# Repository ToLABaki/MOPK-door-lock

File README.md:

# MOPK-door-lock
The door locking mechanism for the MOPK team

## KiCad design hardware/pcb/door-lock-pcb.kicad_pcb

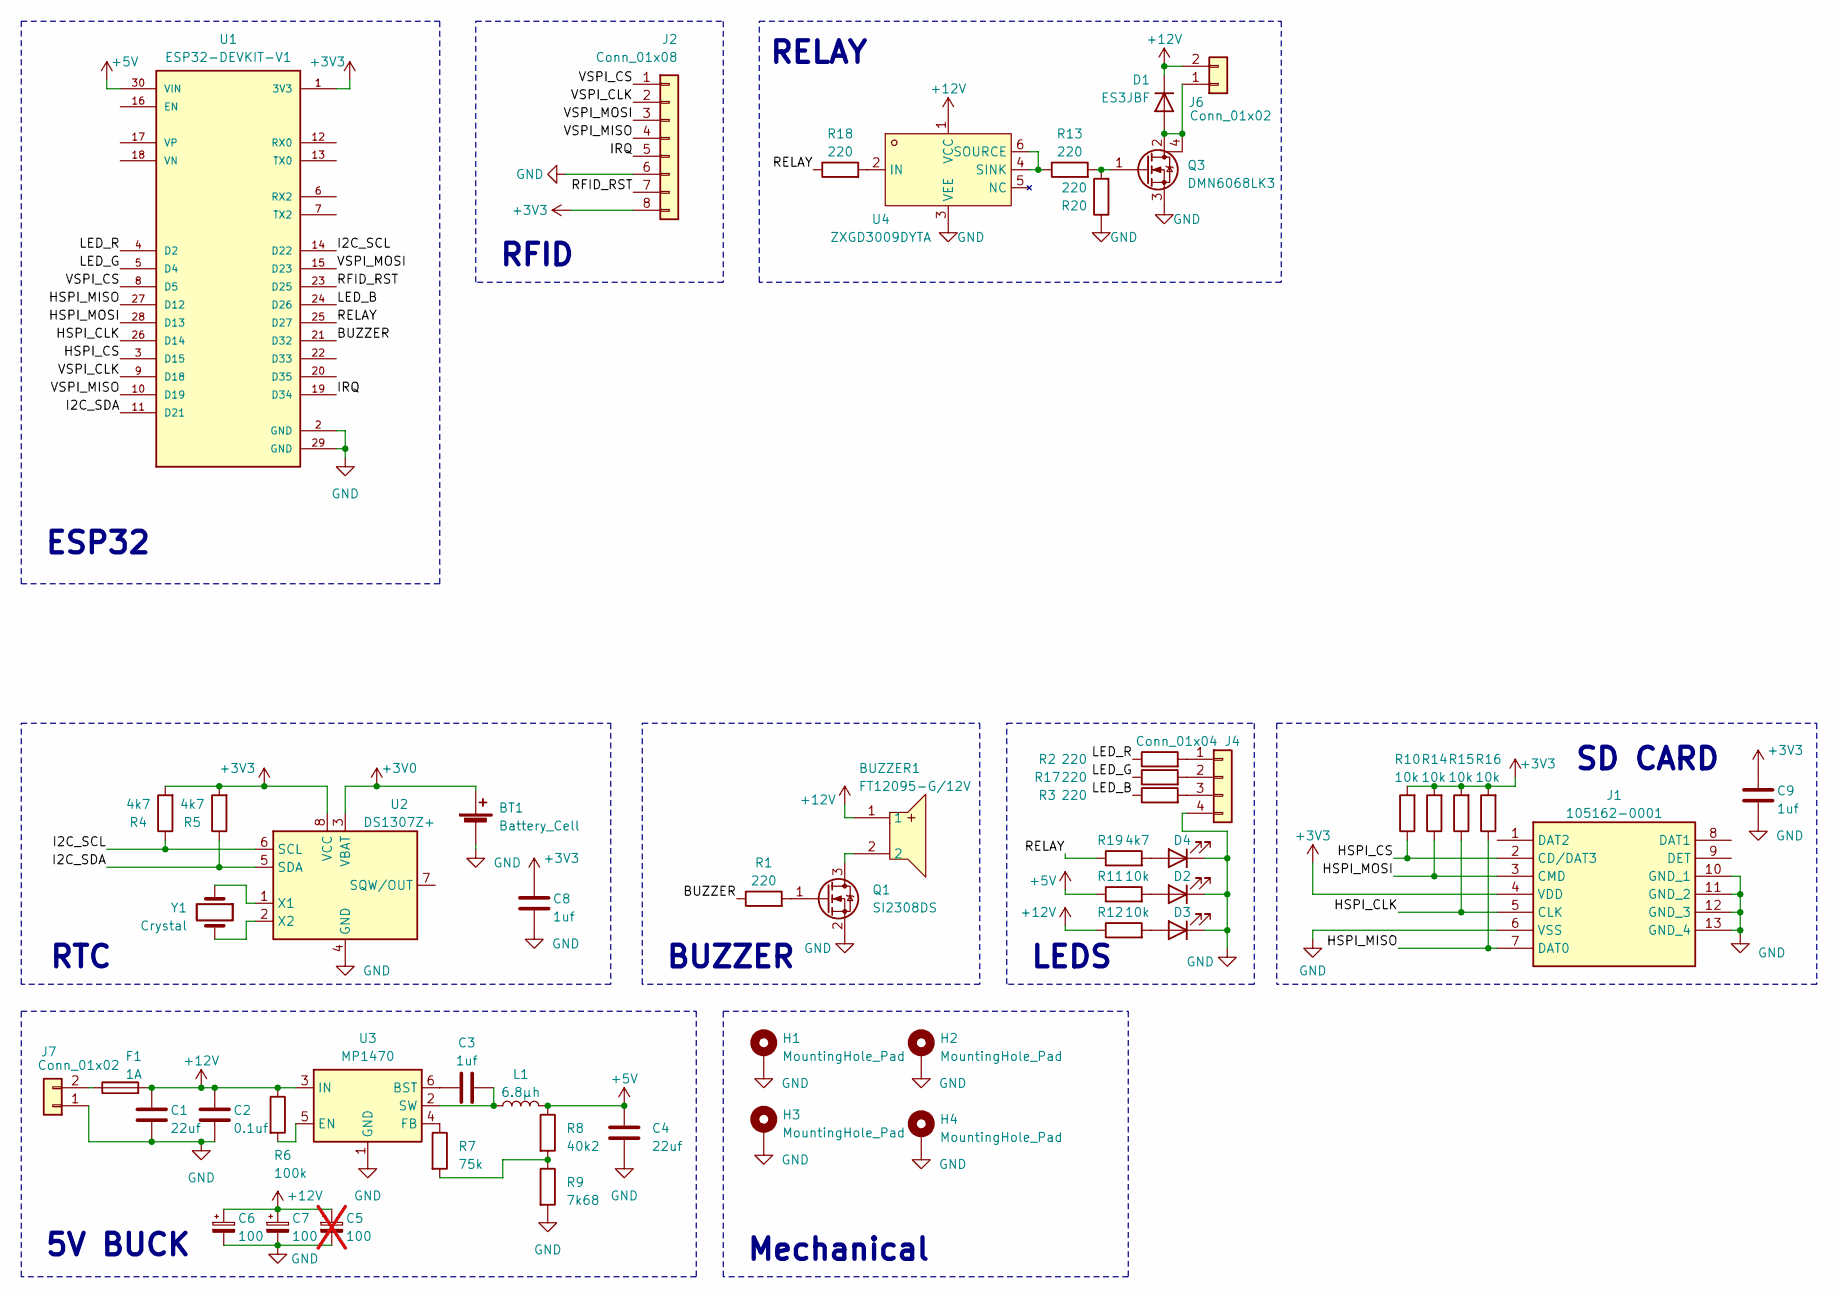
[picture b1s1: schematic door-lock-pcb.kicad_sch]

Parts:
BT1: Battery_Cell; BAT-SMD_CR1220-2; LCSC C70381
BUZZER1: FT12095-G/12V; BUZ-TH_BD12.0-P7.60-D0.6-FD; LCSC C781867
C1, C4: 22uf; C_1206_3216Metric_Pad1.33x1.80mm_HandSolder
C2: 0.1uf; C_0805_2012Metric_Pad1.18x1.45mm_HandSolder
C3, C8, C9: 1uf; C_0805_2012Metric_Pad1.18x1.45mm_HandSolder
C5: 100; CP_Elec_6.3x5.4; LCSC C111600; not fitted
C6, C7: 100; CP_Elec_6.3x5.4; LCSC C111600
D1: ES3JBF; D_SMC; LCSC C3011135
D2, D3, D4: LED_0805_2012Metric_Pad1.15x1.40mm_HandSolder
F1: 1A; FUSE-TH_L22.6-W9.0; LCSC C3131
H1, H2, H3, H4: MountingHole_Pad; MountingHole_3.2mm_M3_Pad_Via
J1: 105162-0001; TF-SMD_TF-PUSH; Mouser Part Number 538-105162-0001
J2: Conn_01x08; JST_XH_B8B-XH-A_1x08_P2.50mm_Vertical
J4: Conn_01x04; JST_XH_B4B-XH-A_1x04_P2.50mm_Vertical
J6, J7: Conn_01x02; JST_XH_B2B-XH-A_1x02_P2.50mm_Vertical
L1: 6.8μh; IND-SMD_L7.2-W6.6_GPSR07X0; LCSC C5189755
Q1: SI2308DS; SOT-23_Handsoldering
Q3: DMN6068LK3; TO-252-3_TabPin4; LCSC C154756
R1, R2, R3, R13, R17, R18, R20: 220; R_0805_2012Metric_Pad1.20x1.40mm_HandSolder
R4, R5, R19: 4k7; R_0805_2012Metric_Pad1.20x1.40mm_HandSolder
R6: 100k; R_0805_2012Metric_Pad1.20x1.40mm_HandSolder
R7: 75k; R_0805_2012Metric_Pad1.20x1.40mm_HandSolder
R8: 40k2; R_0805_2012Metric_Pad1.20x1.40mm_HandSolder
R9: 7k68; R_0805_2012Metric_Pad1.20x1.40mm_HandSolder
R10, R11, R12, R14, R15, R16: 10k; R_0805_2012Metric_Pad1.20x1.40mm_HandSolder
U1: ESP32-DEVKIT-V1; MODULE_ESP32_DEVKIT_V1; PARTREV N/A
U2: DS1307Z+; SOIC-8_3.9x4.9mm_P1.27mm; LCSC C5145427
U3: MP1470; TSOT-23-6; LCSC C558426
U4: ZXGD3009DYTA; SOT-363_SC-70-6; LCSC Part C441818
Y1: Crystal; Crystal_C38-LF_D3.0mm_L8.0mm_Horizontal; LCSC C2992632

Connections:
+3V0: BT1.1 (+), U2.3 (VBAT)
+3V3: C8.1, C9.1, J1.4 (VDD), J2.8, R4.2, R5.2, R10.2, R14.2, R15.2, R16.2, U1.1 (3V3), U2.8 (VCC)
+5V: C4.1, L1.2, R8.1, R11.1, U1.30 (VIN)
+12V: BUZZER1.1, C1.1, C2.1, C5.1, C6.1, C7.1, D1.1 (K), F1.2, J6.2, R6.1, R12.1, U3.3 (IN), U4.1 (VCC)
/BUZZER: R1.1, U1.21 (D32)
/HSPI_CLK: J1.5 (CLK), R15.1, U1.26 (D14)
/HSPI_CS: J1.2 (CD/DAT3), R10.1, U1.3 (D15)
/HSPI_MISO: J1.7 (DAT0), R16.1, U1.27 (D12)
/HSPI_MOSI: J1.3 (CMD), R14.1, U1.28 (D13)
/I2C_SCL: R4.1, U1.14 (D22), U2.6 (SCL)
/I2C_SDA: R5.1, U1.11 (D21), U2.5 (SDA)
/IRQ: J2.5, U1.19 (D34)
/LED_B: R3.1, U1.24 (D26)
/LED_G: R17.1, U1.5 (D4)
/LED_R: R2.1, U1.4 (D2)
/RELAY: R18.1, R19.1, U1.25 (D27)
/RFID_RST: J2.7, U1.23 (D25)
/VSPI_CLK: J2.2, U1.9 (D18)
/VSPI_CS: J2.1, U1.8 (D5)
/VSPI_MISO: J2.4, U1.10 (D19)
/VSPI_MOSI: J2.3, U1.15 (D23)
GND: BT1.2 (-), C1.2, C2.2, C4.2, C5.2, C6.2, C7.2, C8.2, C9.2, D2.1 (K), D3.1 (K), D4.1 (K), H1.1, H2.1, H3.1, H4.1, J1.6 (VSS), J1.10 (GND_1), J1.11 (GND_2), J1.12 (GND_3), J1.13 (GND_4), J2.6, J4.4, J7.1, Q1.2 (S), Q3.3 (S), R9.2, R20.1, U1.2 (GND), U1.29 (GND), U2.4 (GND), U3.1 (GND), U4.3 (VEE)
unnamed: D1.2 (A), J6.1, Q3.2 (D), Q3.4 (D)
unnamed: D2.2 (A), R11.2
unnamed: D3.2 (A), R12.2
unnamed: D4.2 (A), R19.2
unnamed: J4.1, R2.2
unnamed: J4.2, R17.2
unnamed: J4.3, R3.2
unnamed: F1.1, J7.2
unnamed: BUZZER1.2, Q1.3 (D)
unnamed: Q1.1 (G), R1.2
unnamed: Q3.1 (G), R13.2, R20.2
unnamed: R7.2, R8.2, R9.1
unnamed: U2.1 (X1), Y1.1
unnamed: U2.2 (X2), Y1.2
unnamed: C3.1, U3.6 (BST)
unnamed: R6.2, U3.5 (EN)
unnamed: R7.1, U3.4 (FB)
unnamed: C3.2, L1.1, U3.2 (SW)
unnamed: R18.2, U4.2 (IN)
unnamed: R13.1, U4.4 (SINK), U4.6 (SOURCE)

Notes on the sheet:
5V BUCK
RTC
RFID
SD CARD
ESP32
LEDS
BUZZER
Mechanical
RELAY

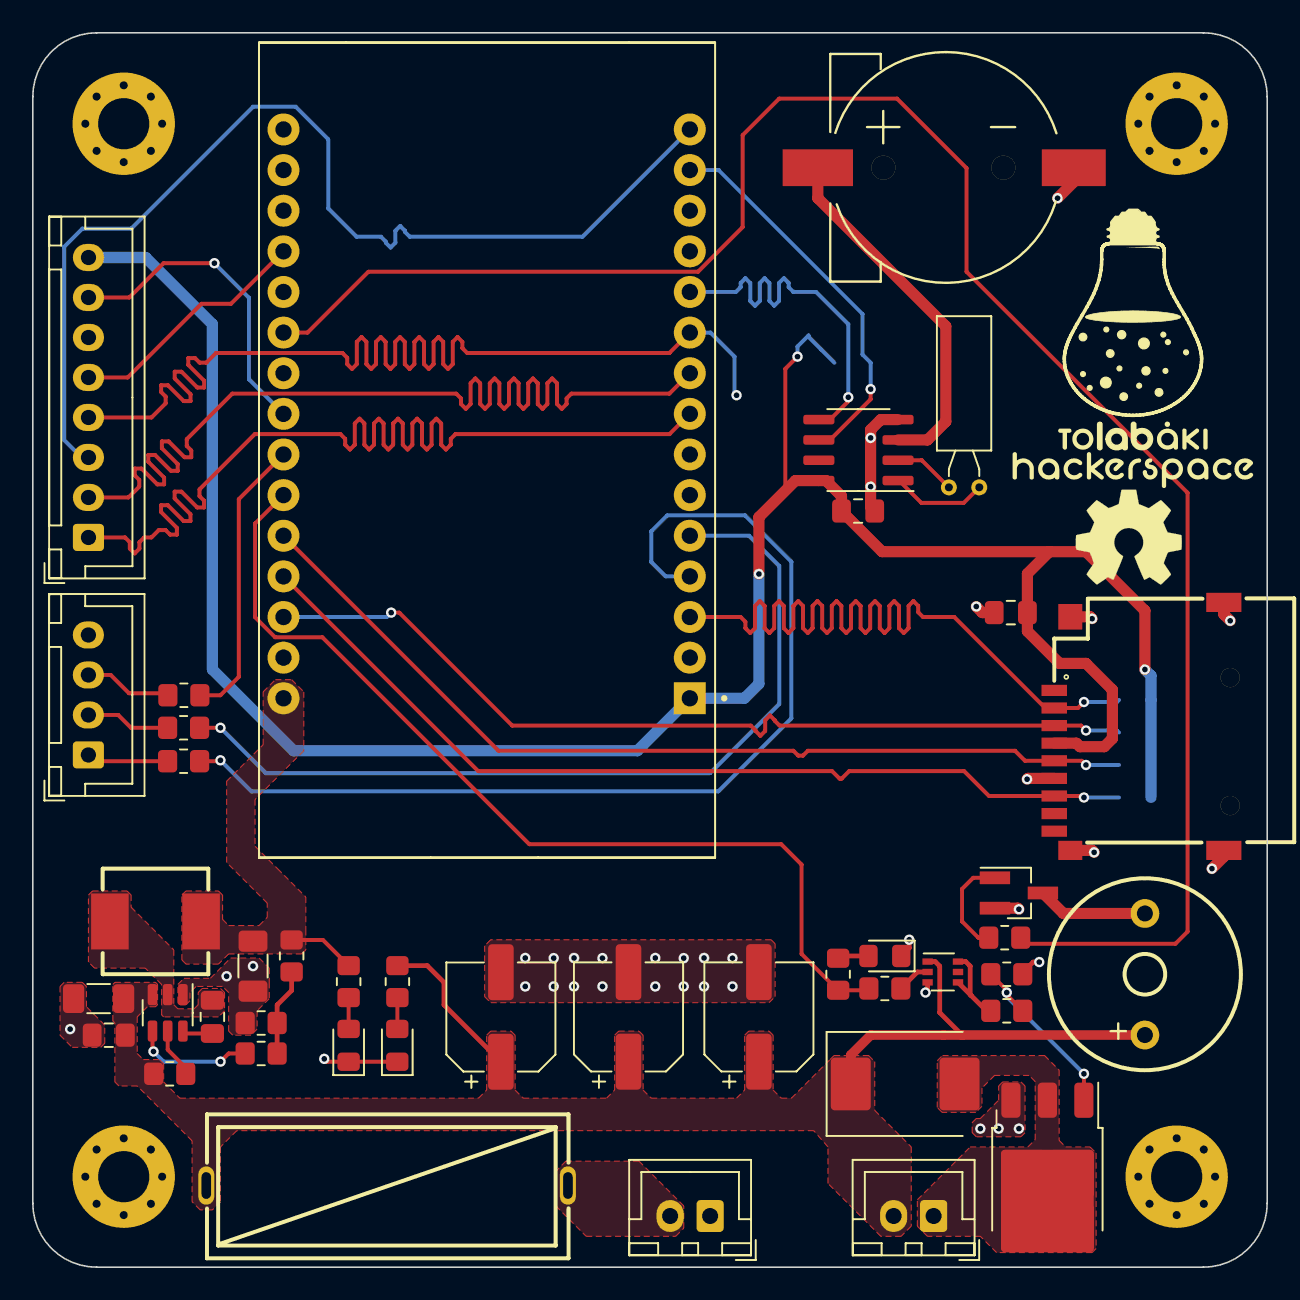
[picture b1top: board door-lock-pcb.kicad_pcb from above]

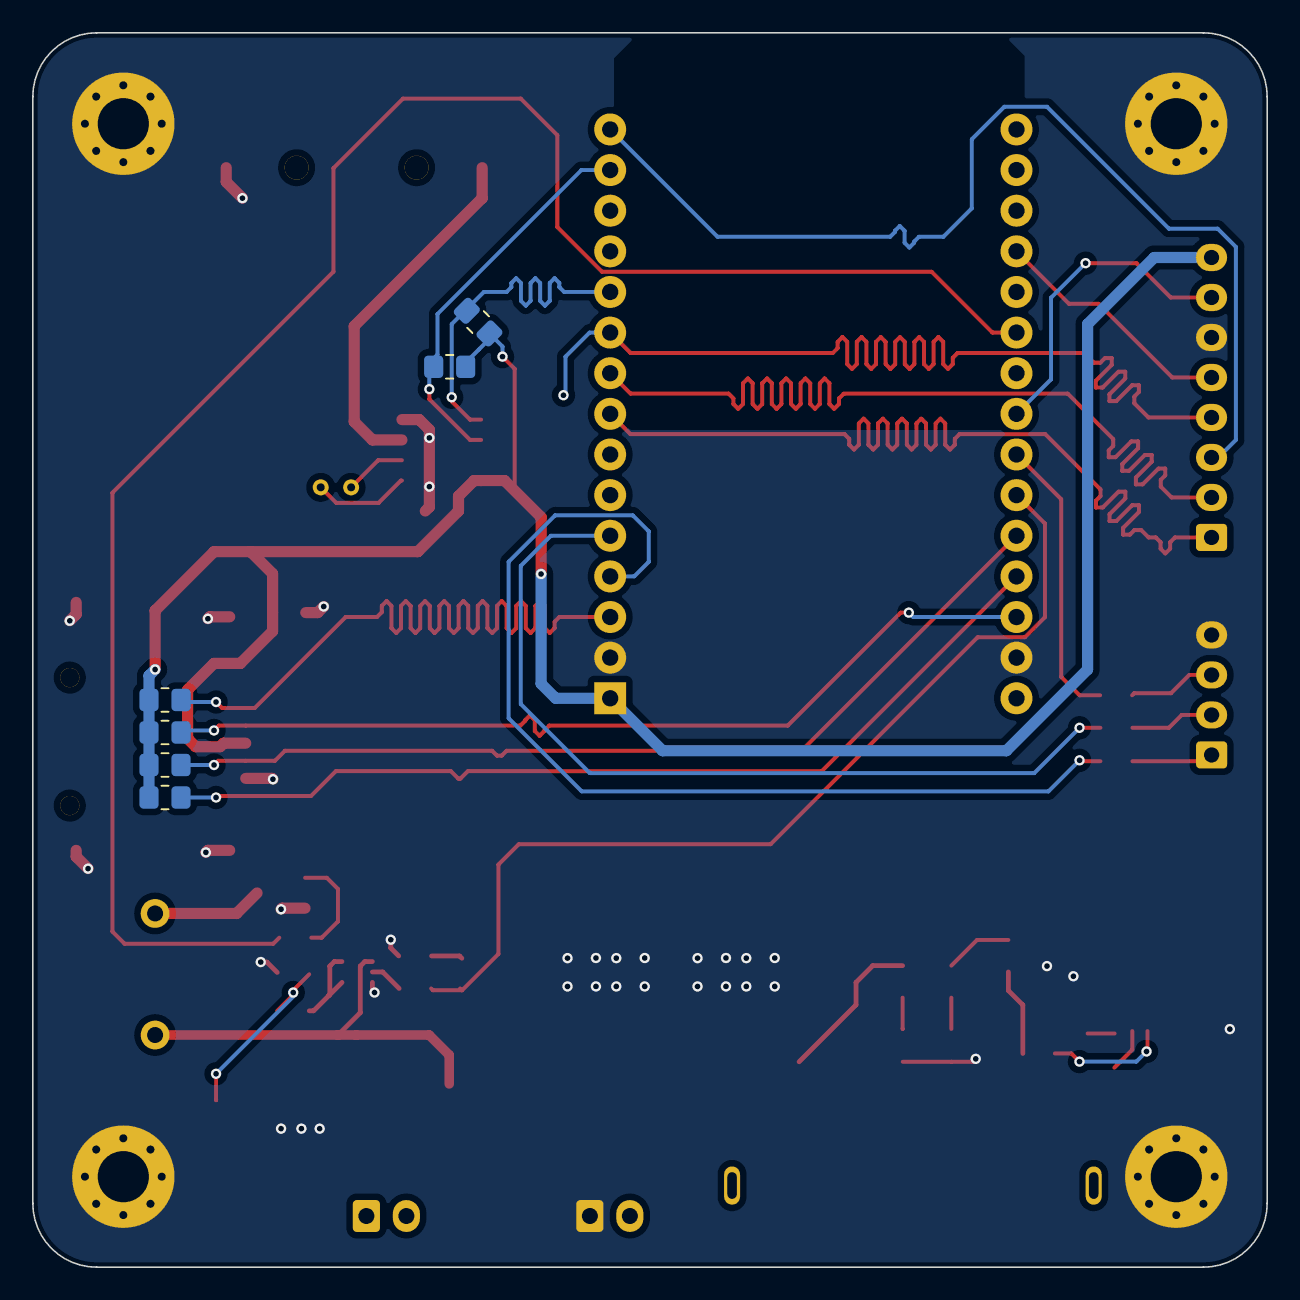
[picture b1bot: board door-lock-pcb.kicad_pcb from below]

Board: 2 copper layers, 77.2 x 77.2 mm, 53 parts (6 on the bottom side), 42 nets.

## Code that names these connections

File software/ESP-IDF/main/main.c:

#include <stdbool.h>
#include <stdio.h>
#include <stdlib.h>
#include <string.h>

#include "freertos/FreeRTOS.h"
#include "freertos/task.h"
#include "esp_freertos_hooks.h"
#include "freertos/semphr.h"
#include "freertos/timers.h"
#include "esp_system.h"
#include "driver/gpio.h"
#include "esp_err.h"
#include "esp_log.h"
#include "esp_spiffs.h"
#include "driver/i2c.h"

#include "sd_spi.h"
#include "MFRC522.h"


static void mainTask(void *pvParameter);

#define HSPI_MISO   GPIO_NUM_12
#define HSPI_CLK    GPIO_NUM_14
#define HSPI_MOSI    GPIO_NUM_13

#define RELAY_PIN       GPIO_NUM_27
#define BUZZER_PIN       GPIO_NUM_32

#define LED_R           GPIO_NUM_26
#define LED_G           GPIO_NUM_4
#define LED_B           GPIO_NUM_2

#define RTC_ADDR        0x68

static const char *TAG = "i2c-example";


gpio_config_t io_conf_out = {
    .intr_type = GPIO_INTR_DISABLE,
    .mode = GPIO_MODE_OUTPUT,
    .pin_bit_mask = (1ULL<<RELAY_PIN) | (1ULL<<BUZZER_PIN) | (1ULL<<LED_R) | (1ULL<<LED_G) | (1ULL<<LED_B),
    .pull_down_en = 0,
    .pull_up_en = 0

};

gpio_config_t io_conf_HSPI = {
    .intr_type = GPIO_INTR_DISABLE,
    .mode = GPIO_MODE_OUTPUT,
    .pin_bit_mask = (1ULL<<HSPI_MISO) | (1ULL<<HSPI_CLK) | (1ULL<<HSPI_MOSI),
    .pull_down_en = 0,
    .pull_up_en = 1

};


spi_bus_config_t buscfg={
    .miso_io_num=HSPI_MISO,
    .sclk_io_num=HSPI_CLK,
    .mosi_io_num=HSPI_MOSI,
    .quadwp_io_num = -1,
    .quadhd_io_num = -1,
    .max_transfer_sz = 4000
    
};


esp_err_t spi_init(){
    esp_err_t ret = ESP_OK;
    ret = spi_bus_initialize(HSPI_HOST, &buscfg, SPI_DMA_CH_AUTO);
    if(ret != ESP_OK){
        printf("SPI INT ERR\n");
    }
    return ret;
}



MFRC522Ptr_t mfrc;



uint8_t rx_data[8];

i2c_config_t conf = {
    .mode = I2C_MODE_MASTER,
    .sda_io_num = 21,
    .scl_io_num = 22,
    .sda_pullup_en = GPIO_PULLUP_ENABLE,
    .scl_pullup_en = GPIO_PULLUP_ENABLE,
    .master.clk_speed = 900000
};


	

	

void app_main(void){
    gpio_config(&io_conf_HSPI);
    vTaskDelay(1000/portTICK_PERIOD_MS);
    FILE *f = NULL;



    spi_init();
    if(sd_init() == ESP_OK){
        printf("SD INIT\n");
        f = fopen("/sdcard/FOO.TXT", "r");
        if(f == NULL){
            printf("File error!\n");
           
        }else{
            printf("File opened\n");
            fclose(f);
        }
    }
    gpio_config(&io_conf_out);
    gpio_set_level(RELAY_PIN, 0);



    gpio_set_level(LED_R, 1);
    gpio_set_level(LED_G, 0);
    gpio_set_level(LED_B, 0);
    vTaskDelay(500/portTICK_PERIOD_MS);
    gpio_set_level(LED_R, 0);
    gpio_set_level(LED_G, 1);
    gpio_set_level(LED_B, 0);
    vTaskDelay(500/portTICK_PERIOD_MS);
    gpio_set_level(LED_R, 0);
    gpio_set_level(LED_G, 0);
    gpio_set_level(LED_B, 1);
    vTaskDelay(500/portTICK_PERIOD_MS);
    gpio_set_level(LED_R, 0);
    gpio_set_level(LED_G, 0);
    gpio_set_level(LED_B, 0);

    mfrc = MFRC522_Init();
    PCD_Init(mfrc);


  

    

    xTaskCreatePinnedToCore(mainTask, "mainTask", 4096*2, NULL, tskIDLE_PRIORITY, NULL,0);


}




void mainTask(void *pvParameter){
    uint32_t i = 0, status = 0;
    uint8_t tmp;
    while(1){
        
        if(PICC_IsNewCardPresent(mfrc) == 1){

            printf("READING\n");
            vTaskDelay(50/portTICK_PERIOD_MS);
            printf("%d  %x-%x-%x-%x  %x\n",PICC_ReadCardSerial(mfrc) , mfrc->uid.uidByte[0], mfrc->uid.uidByte[1], mfrc->uid.uidByte[2], mfrc->uid.uidByte[3], mfrc->uid.sak );
            status = 1;
            i = 0;
        }else{
            //printf("NO\n");
            i++;
            if(i == 2){
                status = 0;
                i = 0;
            }
        }

        if(status == 1){
            //tag detected
            gpio_set_level(RELAY_PIN, 1);
            //ESP_LOG_BUFFER_HEX(TAG, rx_data, 8);
            gpio_set_level(LED_G, 1);
            gpio_set_level(LED_R, 0);
            gpio_set_level(BUZZER_PIN, 1);

            vTaskDelay(700/portTICK_PERIOD_MS);
        }else{
            //nothing detected
            gpio_set_level(BUZZER_PIN, 0);
            gpio_set_level(LED_G, 0);
            gpio_set_level(LED_R, 1);
            gpio_set_level(RELAY_PIN, 0);
            
        }
        vTaskDelay(20/portTICK_PERIOD_MS);
    }
    vTaskDelete(NULL);
}

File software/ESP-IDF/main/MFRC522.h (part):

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#include "esp_timer.h"


#define VSPI_CS GPIO_NUM_5
#define RST_PIN GPIO_NUM_25
#define VSPI_MOSI GPIO_NUM_23
#define VSPI_MISO GPIO_NUM_19
#define VSPI_CLK  GPIO_NUM_18

/*******************************************************************************
 * Types/enumerations/variables
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
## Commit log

2023-09-17 organized files + started on the pcb
2023-09-17 added ESP-IDF 5 template project + moved stuff around
2023-09-20 started on porting a library for MFRC522 chip
2023-09-23 finished rfid library, dunno if it works
2023-09-24 progress with the PCB
2023-09-24 added a mosfet for the solenoid + upgraded he fuse
2023-09-29 finished rev 1 of pcb + ported MFRC522 library to ESP-IDF + finished the BOM
2023-10-27 changed mosfet driver + connected sd to pwr
2023-10-27 changed gitignore
2023-10-27 removed backups
2023-11-16 fixed error with mosfet drain
2023-12-13 progress with sd card
2024-03-19 test firmware that accepts everyone
2024-03-20 added schematic pdf

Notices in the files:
software/ESP-IDF/main/MFRC522.h:
The original library is released to the public domain.
